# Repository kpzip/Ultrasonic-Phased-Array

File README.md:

# Ultrasonic-Phased-Array
play the vine boom with high precision

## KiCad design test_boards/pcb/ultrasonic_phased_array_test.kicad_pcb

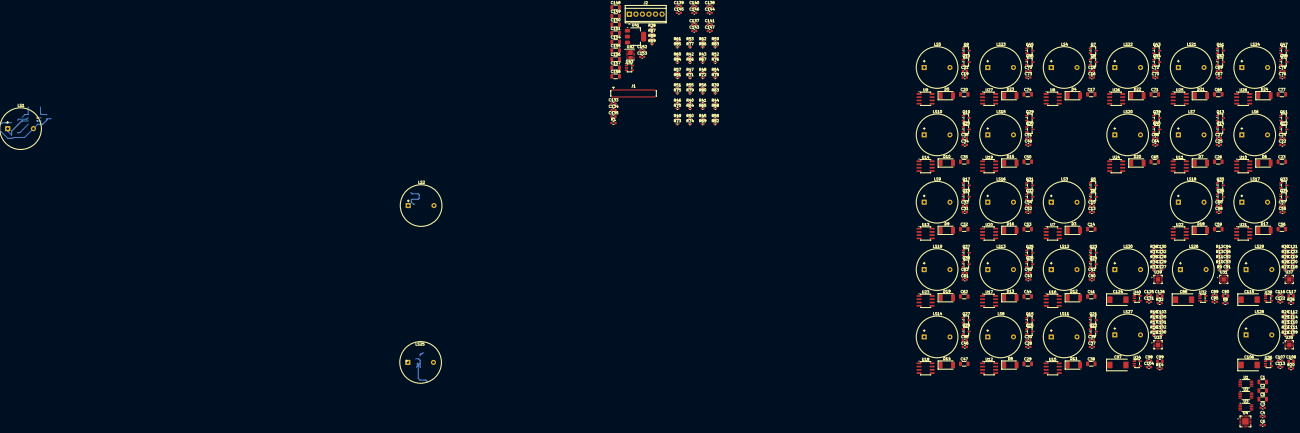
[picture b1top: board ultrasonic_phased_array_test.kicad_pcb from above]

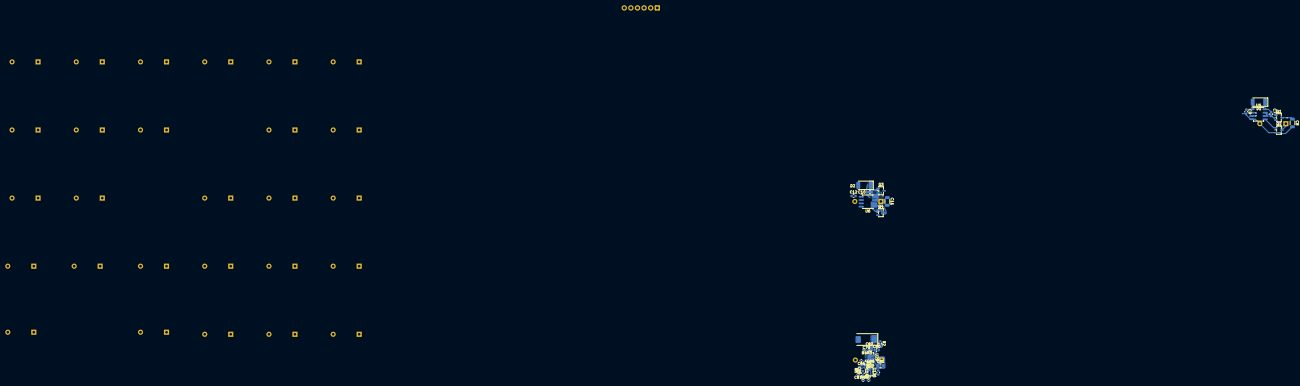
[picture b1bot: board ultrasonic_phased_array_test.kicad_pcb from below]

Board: 4 copper layers, 394 parts (33 on the bottom side), 298 nets.

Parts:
C1, C5, C148, C150, C151, C154, C155: 10μF; C_1206_3216Metric
C2, C156, C157, C158: 1μF; C_1206_3216Metric
C3, C4, C6, C9, C12, C15, C18, C21, C24, C27, C30, C33, C36, C39, C42, C45, C48, C51, C54, C57, C60, C63, C66, C69, C72, C75, C78, C80, C89, C98, C107, C116, C125, C133, C134, C135, C136, C137, C138, C139, C140, C141, C142, C143, C144, C145, C146, C147: 100nF; C_0603_1608Metric
C7, C10, C13, C16, C19, C22, C25, C28, C31, C34, C37, C40, C43, C46, C49, C52, C55, C58, C61, C64, C67, C70, C73, C76: 470nF; C_0603_1608Metric
C8, C11, C14, C17, C20, C23, C26, C29, C32, C35, C38, C41, C44, C47, C50, C53, C56, C59, C62, C65, C68, C71, C74, C77: 100nF; C_1206_3216Metric
C79, C88, C97, C106, C115, C124: 100μF; CP_EIA-7343-31_Kemet-D
C81, C90, C99, C108, C117, C126: 22nF; C_0805_2012Metric
C82, C91, C100, C109, C118, C127: 220pF; C_0402_1005Metric
C83, C84, C85, C87, C92, C93, C94, C96, C101, C102, C103, C105, C110, C111, C112, C114, C119, C120, C121, C123, C128, C129, C130, C132: 1nF; C_0402_1005Metric
C86, C95, C104, C113, C122, C131: 150nF; C_0603_1608Metric
C149: 22μF; C_1206_3216Metric
C152, C153: 10nF; C_0603_1608Metric
D1, D2, D3, D4, D5, D6, D7, D8, D9, D10, D11, D12, D13, D14, D15, D16, D17, D18, D19, D20, D21, D22, D23, D24: SUF4007; D_MELF
J1: DF40C-80DP-0.4V; Hirose_DF40C-80DP-0.4V_2x40-1MP_P0.4mm
J2: Screw_Terminal_01x06; TerminalBlock_TE_282834-6_1x06_P2.54mm_Horizontal
LS1, LS2, LS3, LS4, LS5, LS6, LS7, LS8, LS9, LS10, LS11, LS12, LS13, LS14, LS15, LS16, LS17, LS18, LS19, LS20, LS21, LS22, LS23, LS24, LS25, LS26, LS27, LS28, LS29, LS30: Speaker_Ultrasound; Ultrasonic_Transducer_D16mm_H7mm_P10mm
Q1, Q2, Q3, Q4, Q5, Q6, Q7, Q8, Q9, Q10, Q11, Q12, Q13, Q14, Q15, Q16, Q17, Q18, Q19, Q20, Q21, Q22, Q23, Q24, Q25, Q26, Q27, Q28, Q29, Q30, Q31, Q32, Q33, Q34, Q35, Q36, Q37, Q38, Q39, Q40, Q41, Q42, Q43, Q44, Q45, Q46, Q47, Q48: G2003A; SOT-23-3
R1, R2, R8, R14, R20, R26, R32: 10Ω; R_0603_1608Metric
R3, R9, R15, R21, R27, R33: 30kΩ; R_0402_1005Metric
R4, R10, R16, R22, R28, R34: 56kΩ; R_0402_1005Metric
R5, R11, R17, R23, R29, R35: 31.6kΩ; R_0402_1005Metric
R6, R12, R18, R24, R30, R36: 15.8kΩ; R_0402_1005Metric
R7, R13, R19, R25, R31, R37: 511Ω; R_0402_1005Metric
R38, R89: 24.3Ω; R_0402_1005Metric
R39, R40, R41, R42, R43, R44, R45, R46, R47, R48, R49, R50, R51, R52, R53, R54, R55, R56, R57, R58, R59, R60, R61, R62, R63, R64, R65, R66, R67, R68, R69, R70, R71, R72, R73, R74, R75, R76, R77, R78, R79, R80, R81, R82, R83, R84, R85, R86: 10kΩ; R_0402_1005Metric
R87, R88: 25.5Ω; R_0402_1005Metric
U1, U2, U3: OPA2626; Texas_S-PDSO-G8_3x3mm_P0.65mm
U4: AD7689xCP; LFCSP-20-1EP_4x4mm_P0.5mm_EP2.5x2.5mm
U5, U6, U7, U8, U9, U10, U11, U12, U13, U14, U15, U16, U17, U18, U19, U20, U21, U22, U23, U24, U25, U26, U27, U28: EG2131D; SOP-8_3.76x4.96mm_P1.27mm
U29, U31, U33, U35, U37, U39: LOG300RGT; VQFN-16-1EP_3x3mm_P0.5mm_EP1.68x1.68mm
U30, U32, U34, U36, U38, U40: OPA388xxDBV; SOT-23-5
U41: AZ1117CH-3.3; SOT-223-3_TabPin2
U42: LT3032; Linear_DE14MA
U43: TPS60401DBV; SOT-23-5

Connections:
+2.5V: C136.2, C137.2, C138.2, C139.2, C140.2, C141.2, C152.2, C154.2, R87.1, U30.5 (V+), U32.5 (V+), U34.5 (V+), U36.5 (V+), U38.5 (V+), U40.5 (V+), U42.1 (OUTP)
+3.3V: C3.2, C4.2, C149.1, U4.15 (VIO), U41.2 (OUT)
+5V: C1.2, C133.2, C134.2, C135.2, C148.2, C150.2, C158.2, J2.2, R1.2, R2.1, R8.1, R14.1, R20.1, R26.1, R32.1, U1.8 (V+), U2.8 (V+), U3.8 (V+), U41.3 (IN), U42.10 (~SHDNN), U42.12 (~SHDNP), U42.14 (INP), U43.2 (IN)
-2.5V: C142.1, C143.1, C144.1, C145.1, C146.1, C147.1, C153.2, C155.1, R88.2, U30.2 (V-), U32.2 (V-), U34.2 (V-), U36.2 (V-), U38.2 (V-), U40.2 (V-), U42.7 (OUTN)
-5V: C151.1, C157.2, U42.6 (INN), U42.9 (INN), U43.1 (OUT)
/ADC_CNV: J1.76, U4.11 (CNV)
/ADC_DIN: J1.77, U4.12 (DIN)
/ADC_SCK: J1.78, U4.13 (SCK)
/ADC_SDO: J1.75, U4.14 (SDO)
/Power & Regulators/ADJN: R88.1, R89.2, U42.8 (ADJN)
/Power & Regulators/ADJP: R38.1, R87.2, U42.2 (ADJP)
/TX1_HIN: J1.4, R39.2
/TX1_~LIN: J1.6, R63.1
/TX2_HIN: J1.10, R40.2
/TX2_~LIN: J1.12, R64.1
/TX3_HIN: J1.16, R41.2
/TX3_~LIN: J1.18, R65.1
/TX4_HIN: J1.22, R42.2
/TX4_~LIN: J1.24, R66.1
/TX5_HIN: J1.28, R43.2
/TX5_~LIN: J1.30, R67.1
/TX6_HIN: J1.34, R44.2
/TX6_~LIN: J1.36, R68.1
/TX7_HIN: J1.40, R45.2
/TX7_~LIN: J1.42, R69.1
/TX8_HIN: J1.46, R46.2
/TX8_~LIN: J1.48, R70.1
/TX9_HIN: J1.52, R47.2
/TX9_~LIN: J1.54, R71.1
/TX10_HIN: J1.58, R48.2
/TX10_~LIN: J1.60, R72.1
/TX11_HIN: J1.64, R49.2
/TX11_~LIN: J1.66, R73.1
/TX12_HIN: J1.70, R50.2
/TX12_~LIN: J1.72, R74.1
/TX13_HIN: J1.69, R51.2
/TX13_~LIN: J1.71, R75.1
/TX14_HIN: J1.63, R52.2
/TX14_~LIN: J1.65, R76.1
/TX15_HIN: J1.57, R53.2
/TX15_~LIN: J1.59, R77.1
/TX16_HIN: J1.51, R54.2
/TX16_~LIN: J1.53, R78.1
/TX17_HIN: J1.45, R55.2
/TX17_~LIN: J1.47, R79.1
/TX18_HIN: J1.39, R56.2
/TX18_~LIN: J1.41, R80.1
/TX19_HIN: J1.33, R57.2
/TX19_~LIN: J1.35, R81.1
/TX20_HIN: J1.27, R58.2
/TX20_~LIN: J1.29, R82.1
/TX21_HIN: J1.21, R59.2
/TX21_~LIN: J1.23, R83.1
/TX22_HIN: J1.15, R60.2
/TX22_~LIN: J1.17, R84.1
/TX23_HIN: J1.9, R61.2
/TX23_~LIN: J1.11, R85.1
/TX24_HIN: J1.3, R62.2
/TX24_~LIN: J1.5, R86.1
/Transducer Rx 1/OUTN: U1.3 (+), U29.6 (~BUFF)
/Transducer Rx 2/OUTN: U1.5 (+), U31.6 (~BUFF)
/Transducer Rx 3/OUTN: U2.3 (+), U33.6 (~BUFF)
/Transducer Rx 4/OUTN: U2.5 (+), U35.6 (~BUFF)
/Transducer Rx 5/OUTN: U3.3 (+), U37.6 (~BUFF)
/Transducer Rx 6/OUTN: U3.5 (+), U39.6 (~BUFF)
/Transducer Tx 1/HIN_IN: R39.1, U5.2 (HIN)
/Transducer Tx 1/~LIN_IN: R63.2, U5.3 (~LIN)
/Transducer Tx 2/HIN_IN: R40.1, U6.2 (HIN)
/Transducer Tx 2/~LIN_IN: R64.2, U6.3 (~LIN)
/Transducer Tx 3/HIN_IN: R41.1, U7.2 (HIN)
/Transducer Tx 3/~LIN_IN: R65.2, U7.3 (~LIN)
/Transducer Tx 4/HIN_IN: R42.1, U8.2 (HIN)
/Transducer Tx 4/~LIN_IN: R66.2, U8.3 (~LIN)
/Transducer Tx 5/HIN_IN: R43.1, U9.2 (HIN)
/Transducer Tx 5/~LIN_IN: R67.2, U9.3 (~LIN)
/Transducer Tx 6/HIN_IN: R44.1, U10.2 (HIN)
/Transducer Tx 6/~LIN_IN: R68.2, U10.3 (~LIN)
/Transducer Tx 7/HIN_IN: R45.1, U11.2 (HIN)
/Transducer Tx 7/~LIN_IN: R69.2, U11.3 (~LIN)
/Transducer Tx 8/HIN_IN: R46.1, U12.2 (HIN)
/Transducer Tx 8/~LIN_IN: R70.2, U12.3 (~LIN)
/Transducer Tx 9/HIN_IN: R47.1, U13.2 (HIN)
/Transducer Tx 9/~LIN_IN: R71.2, U13.3 (~LIN)
/Transducer Tx 10/HIN_IN: R48.1, U14.2 (HIN)
/Transducer Tx 10/~LIN_IN: R72.2, U14.3 (~LIN)
/Transducer Tx 11/HIN_IN: R49.1, U15.2 (HIN)
/Transducer Tx 11/~LIN_IN: R73.2, U15.3 (~LIN)
/Transducer Tx 12/HIN_IN: R50.1, U16.2 (HIN)
/Transducer Tx 12/~LIN_IN: R74.2, U16.3 (~LIN)
/Transducer Tx 13/HIN_IN: R51.1, U17.2 (HIN)
/Transducer Tx 13/~LIN_IN: R75.2, U17.3 (~LIN)
/Transducer Tx 14/HIN_IN: R52.1, U18.2 (HIN)
/Transducer Tx 14/~LIN_IN: R76.2, U18.3 (~LIN)
/Transducer Tx 15/HIN_IN: R53.1, U19.2 (HIN)
/Transducer Tx 15/~LIN_IN: R77.2, U19.3 (~LIN)
/Transducer Tx 16/HIN_IN: R54.1, U20.2 (HIN)
/Transducer Tx 16/~LIN_IN: R78.2, U20.3 (~LIN)
/Transducer Tx 17/HIN_IN: R55.1, U21.2 (HIN)
/Transducer Tx 17/~LIN_IN: R79.2, U21.3 (~LIN)
/Transducer Tx 18/HIN_IN: R56.1, U22.2 (HIN)
/Transducer Tx 18/~LIN_IN: R80.2, U22.3 (~LIN)
/Transducer Tx 19/HIN_IN: R57.1, U23.2 (HIN)
/Transducer Tx 19/~LIN_IN: R81.2, U23.3 (~LIN)
/Transducer Tx 20/HIN_IN: R58.1, U24.2 (HIN)
/Transducer Tx 20/~LIN_IN: R82.2, U24.3 (~LIN)
/Transducer Tx 21/HIN_IN: R59.1, U25.2 (HIN)
/Transducer Tx 21/~LIN_IN: R83.2, U25.3 (~LIN)
/Transducer Tx 22/HIN_IN: R60.1, U26.2 (HIN)
/Transducer Tx 22/~LIN_IN: R84.2, U26.3 (~LIN)
/Transducer Tx 23/HIN_IN: R61.1, U27.2 (HIN)
/Transducer Tx 23/~LIN_IN: R85.2, U27.3 (~LIN)
/Transducer Tx 24/HIN_IN: R62.1, U28.2 (HIN)
/Transducer Tx 24/~LIN_IN: R86.2, U28.3 (~LIN)
GND: C1.1, C2.1, C3.1, C4.1, C5.1, C6.1, C8.2, C9.2, C11.2, C12.2, C14.2, C15.2, C17.2, C18.2, C20.2, C21.2, C23.2, C24.2, C26.2, C27.2, C29.2, C30.2, C32.2, C33.2, C35.2, C36.2, C38.2, C39.2, C41.2, C42.2, C44.2, C45.2, C47.2, C48.2, C50.2, C51.2, C53.2, C54.2, C56.2, C57.2, C59.2, C60.2, C62.2, C63.2, C65.2, C66.2, C68.2, C69.2, C71.2, C72.2, C74.2, C75.2, C77.2, C78.2, C79.2, C80.1, C82.1, C84.2, C86.1, C88.2, C89.1, C91.1, C93.2, C95.1, C97.2, C98.1, C100.1, C102.2, C104.1, C106.2, C107.1, C109.1, C111.2, C113.1, C115.2, C116.1, C118.1, C120.2, C122.1, C124.2, C125.1, C127.1, C129.2, C131.1, C133.1, C134.1, C135.1, C136.1, C137.1, C138.1, C139.1, C140.1, C141.1, C142.2, C143.2, C144.2, C145.2, C146.2, C147.2, C148.1, C149.2, C157.1, C158.1, J1.1, J1.2, J1.7, J1.8, J1.13, J1.14, J1.19, J1.20, J1.25, J1.26, J1.31, J1.32, J1.37, J1.38, J1.43, J1.44, J1.49, J1.50, J1.55, J1.56, J1.61, J1.62, J1.67, J1.68, J1.73, J1.74, J1.79, J1.80, J2.1, J2.3, J2.5, LS1.2, LS2.2, LS3.2, LS4.2, LS5.2, LS6.2, LS7.2, LS8.2, LS9.2, LS10.2, LS11.2, LS12.2, LS13.2, LS14.2, LS15.2, LS16.2, LS17.2, LS18.2, LS19.2, LS20.2, LS21.2, LS22.2, LS23.2, LS24.2, LS25.2, LS26.2, LS27.2, LS28.2, LS29.2, LS30.2, Q2.2 (S), Q4.2 (S), Q6.2 (S), Q8.2 (S), Q10.2 (S), Q12.2 (S), Q14.2 (S), Q16.2 (S), Q18.2 (S), Q20.2 (S), Q22.2 (S), Q24.2 (S), Q26.2 (S), Q28.2 (S), Q30.2 (S), Q32.2 (S), Q34.2 (S), Q36.2 (S), Q38.2 (S), Q40.2 (S), Q42.2 (S), Q44.2 (S), Q46.2 (S), Q48.2 (S), R3.2, R4.2, R7.2, R9.2, R10.2, R13.2, R15.2, R16.2, R19.2, R21.2, R22.2, R25.2, R27.2, R28.2, R31.2, R33.2, R34.2, R37.2, U1.4 (V-), U2.4 (V-), U3.4 (V-), U4.4 (GND), U4.5 (GND), U4.10 (COM), U4.21 (EPAD), U5.4 (GND), U6.4 (GND), U7.4 (GND), U8.4 (GND), U9.4 (GND), U10.4 (GND), U11.4 (GND), U12.4 (GND), U13.4 (GND), U14.4 (GND), U15.4 (GND), U16.4 (GND), U17.4 (GND), U18.4 (GND), U19.4 (GND), U20.4 (GND), U21.4 (GND), U22.4 (GND), U23.4 (GND), U24.4 (GND), U25.4 (GND), U26.4 (GND), U27.4 (GND), U28.4 (GND), U29.10 (AGND), U29.15 (DGND), U29.17 (EP), U30.3 (+), U31.10 (AGND), U31.15 (DGND), U31.17 (EP), U32.3 (+), U33.10 (AGND), U33.15 (DGND), U33.17 (EP), U34.3 (+), U35.10 (AGND), U35.15 (DGND), U35.17 (EP), U36.3 (+), U37.10 (AGND), U37.15 (DGND), U37.17 (EP), U38.3 (+), U39.10 (AGND), U39.15 (DGND), U39.17 (EP), U40.3 (+), U41.1 (GND), U43.4 (GND)
unnamed: C2.2, R1.1, U4.1 (VDD), U4.20 (VDD)
unnamed: C81.1, LS25.1
unnamed: C83.2, C85.1, R5.2, U30.1
unnamed: C85.2, C87.2, R6.2, R7.1
unnamed: C90.1, LS26.1
unnamed: C92.2, C94.1, R11.2, U32.1
unnamed: C94.2, C96.2, R12.2, R13.1
unnamed: C99.1, LS27.1
unnamed: C101.2, C103.1, R17.2, U34.1
unnamed: C103.2, C105.2, R18.2, R19.1
unnamed: C108.1, LS28.1
unnamed: C110.2, C112.1, R23.2, U36.1
unnamed: C112.2, C114.2, R24.2, R25.1
unnamed: C117.1, LS29.1
unnamed: C119.2, C121.1, R29.2, U38.1
unnamed: C121.2, C123.2, R30.2, R31.1
unnamed: C126.1, LS30.1
unnamed: C128.2, C130.1, R35.2, U40.1
unnamed: C130.2, C132.2, R36.2, R37.1
unnamed: C7.1, D1.1 (K), U5.8 (VB)
unnamed: C10.1, D2.1 (K), U6.8 (VB)
unnamed: C13.1, D3.1 (K), U7.8 (VB)
unnamed: C16.1, D4.1 (K), U8.8 (VB)
unnamed: C19.1, D5.1 (K), U9.8 (VB)
unnamed: C22.1, D6.1 (K), U10.8 (VB)
unnamed: C25.1, D7.1 (K), U11.8 (VB)
unnamed: C28.1, D8.1 (K), U12.8 (VB)
unnamed: C31.1, D9.1 (K), U13.8 (VB)
unnamed: C34.1, D10.1 (K), U14.8 (VB)
unnamed: C37.1, D11.1 (K), U15.8 (VB)
unnamed: C40.1, D12.1 (K), U16.8 (VB)
unnamed: C43.1, D13.1 (K), U17.8 (VB)
unnamed: C46.1, D14.1 (K), U18.8 (VB)
unnamed: C49.1, D15.1 (K), U19.8 (VB)
unnamed: C52.1, D16.1 (K), U20.8 (VB)
unnamed: C55.1, D17.1 (K), U21.8 (VB)
unnamed: C58.1, D18.1 (K), U22.8 (VB)
unnamed: C61.1, D19.1 (K), U23.8 (VB)
unnamed: C64.1, D20.1 (K), U24.8 (VB)
unnamed: C67.1, D21.1 (K), U25.8 (VB)
unnamed: C70.1, D22.1 (K), U26.8 (VB)
unnamed: C73.1, D23.1 (K), U27.8 (VB)
unnamed: C76.1, D24.1 (K), U28.8 (VB)
unnamed: Q1.1 (G), U5.7 (HI)
unnamed: C7.2, LS1.1, Q1.2 (S), Q2.3 (D), U5.6 (SW)
unnamed: Q2.1 (G), U5.5 (LO)
unnamed: Q3.1 (G), U6.7 (HI)
unnamed: C10.2, LS2.1, Q3.2 (S), Q4.3 (D), U6.6 (SW)
unnamed: Q4.1 (G), U6.5 (LO)
unnamed: Q5.1 (G), U7.7 (HI)
unnamed: C13.2, LS3.1, Q5.2 (S), Q6.3 (D), U7.6 (SW)
unnamed: Q6.1 (G), U7.5 (LO)
unnamed: Q7.1 (G), U8.7 (HI)
unnamed: C16.2, LS4.1, Q7.2 (S), Q8.3 (D), U8.6 (SW)
unnamed: Q8.1 (G), U8.5 (LO)
unnamed: Q9.1 (G), U9.7 (HI)
unnamed: C19.2, LS5.1, Q9.2 (S), Q10.3 (D), U9.6 (SW)
unnamed: Q10.1 (G), U9.5 (LO)
unnamed: Q11.1 (G), U10.7 (HI)
unnamed: C22.2, LS6.1, Q11.2 (S), Q12.3 (D), U10.6 (SW)
unnamed: Q12.1 (G), U10.5 (LO)
unnamed: Q13.1 (G), U11.7 (HI)
unnamed: C25.2, LS7.1, Q13.2 (S), Q14.3 (D), U11.6 (SW)
unnamed: Q14.1 (G), U11.5 (LO)
unnamed: Q15.1 (G), U12.7 (HI)
unnamed: C28.2, LS8.1, Q15.2 (S), Q16.3 (D), U12.6 (SW)
unnamed: Q16.1 (G), U12.5 (LO)
unnamed: Q17.1 (G), U13.7 (HI)
unnamed: C31.2, LS9.1, Q17.2 (S), Q18.3 (D), U13.6 (SW)
unnamed: Q18.1 (G), U13.5 (LO)
unnamed: Q19.1 (G), U14.7 (HI)
unnamed: C34.2, LS10.1, Q19.2 (S), Q20.3 (D), U14.6 (SW)
unnamed: Q20.1 (G), U14.5 (LO)
unnamed: Q21.1 (G), U15.7 (HI)
unnamed: C37.2, LS11.1, Q21.2 (S), Q22.3 (D), U15.6 (SW)
unnamed: Q22.1 (G), U15.5 (LO)
unnamed: Q23.1 (G), U16.7 (HI)
unnamed: C40.2, LS12.1, Q23.2 (S), Q24.3 (D), U16.6 (SW)
unnamed: Q24.1 (G), U16.5 (LO)
unnamed: Q25.1 (G), U17.7 (HI)
unnamed: C43.2, LS13.1, Q25.2 (S), Q26.3 (D), U17.6 (SW)
unnamed: Q26.1 (G), U17.5 (LO)
unnamed: Q27.1 (G), U18.7 (HI)
unnamed: C46.2, LS14.1, Q27.2 (S), Q28.3 (D), U18.6 (SW)
unnamed: Q28.1 (G), U18.5 (LO)
unnamed: Q29.1 (G), U19.7 (HI)
unnamed: C49.2, LS15.1, Q29.2 (S), Q30.3 (D), U19.6 (SW)
unnamed: Q30.1 (G), U19.5 (LO)
unnamed: Q31.1 (G), U20.7 (HI)
unnamed: C52.2, LS16.1, Q31.2 (S), Q32.3 (D), U20.6 (SW)
unnamed: Q32.1 (G), U20.5 (LO)
unnamed: Q33.1 (G), U21.7 (HI)
unnamed: C55.2, LS17.1, Q33.2 (S), Q34.3 (D), U21.6 (SW)
unnamed: Q34.1 (G), U21.5 (LO)
unnamed: Q35.1 (G), U22.7 (HI)
unnamed: C58.2, LS18.1, Q35.2 (S), Q36.3 (D), U22.6 (SW)
unnamed: Q36.1 (G), U22.5 (LO)
unnamed: Q37.1 (G), U23.7 (HI)
unnamed: C61.2, LS19.1, Q37.2 (S), Q38.3 (D), U23.6 (SW)
unnamed: Q38.1 (G), U23.5 (LO)
unnamed: Q39.1 (G), U24.7 (HI)
unnamed: C64.2, LS20.1, Q39.2 (S), Q40.3 (D), U24.6 (SW)
unnamed: Q40.1 (G), U24.5 (LO)
unnamed: Q41.1 (G), U25.7 (HI)
unnamed: C67.2, LS21.1, Q41.2 (S), Q42.3 (D), U25.6 (SW)
unnamed: Q42.1 (G), U25.5 (LO)
unnamed: Q43.1 (G), U26.7 (HI)
unnamed: C70.2, LS22.1, Q43.2 (S), Q44.3 (D), U26.6 (SW)
unnamed: Q44.1 (G), U26.5 (LO)
unnamed: Q45.1 (G), U27.7 (HI)
unnamed: C73.2, LS23.1, Q45.2 (S), Q46.3 (D), U27.6 (SW)
unnamed: Q46.1 (G), U27.5 (LO)
unnamed: Q47.1 (G), U28.7 (HI)
unnamed: C76.2, LS24.1, Q47.2 (S), Q48.3 (D), U28.6 (SW)
unnamed: Q48.1 (G), U28.5 (LO)
unnamed: U1.1, U1.2 (-), U4.16 (IN0)
unnamed: U1.6 (-), U1.7, U4.17 (IN1)
unnamed: U2.1, U2.2 (-), U4.18 (IN2)
unnamed: U2.6 (-), U2.7, U4.19 (IN3)
unnamed: U3.1, U3.2 (-), U4.6 (IN4)
unnamed: U3.6 (-), U3.7, U4.7 (IN5)
unnamed: C5.2, U4.2 (REF)
unnamed: C6.2, U4.3 (REFIN)
unnamed: C79.1, C80.2, R2.2, U29.1 (VCC), U29.14 (AFE_EN), U29.16 (LNA_EN)
unnamed: C81.2, U29.13 (LNA_IN)
unnamed: R6.1, U29.11 (LNA_OUT)
unnamed: C84.1, U29.8 (LOG_INN)
unnamed: C83.1, U29.9 (LOG_INP)
unnamed: C82.2, R3.1, U29.2 (LOG_OUT)
unnamed: C86.2, U29.12 (OFFSET_CAP)
unnamed: R4.1, U29.3 (REF_RES)
unnamed: C87.1, R5.1, U30.4 (-)
unnamed: C88.1, C89.2, R8.2, U31.1 (VCC), U31.14 (AFE_EN), U31.16 (LNA_EN)
unnamed: C90.2, U31.13 (LNA_IN)
unnamed: R12.1, U31.11 (LNA_OUT)
unnamed: C93.1, U31.8 (LOG_INN)
unnamed: C92.1, U31.9 (LOG_INP)
unnamed: C91.2, R9.1, U31.2 (LOG_OUT)
unnamed: C95.2, U31.12 (OFFSET_CAP)
unnamed: R10.1, U31.3 (REF_RES)
unnamed: C96.1, R11.1, U32.4 (-)
unnamed: C97.1, C98.2, R14.2, U33.1 (VCC), U33.14 (AFE_EN), U33.16 (LNA_EN)
unnamed: C99.2, U33.13 (LNA_IN)
unnamed: R18.1, U33.11 (LNA_OUT)
unnamed: C102.1, U33.8 (LOG_INN)
unnamed: C101.1, U33.9 (LOG_INP)
unnamed: C100.2, R15.1, U33.2 (LOG_OUT)
unnamed: C104.2, U33.12 (OFFSET_CAP)
unnamed: R16.1, U33.3 (REF_RES)
unnamed: C105.1, R17.1, U34.4 (-)
unnamed: C106.1, C107.2, R20.2, U35.1 (VCC), U35.14 (AFE_EN), U35.16 (LNA_EN)
unnamed: C108.2, U35.13 (LNA_IN)
unnamed: R24.1, U35.11 (LNA_OUT)
unnamed: C111.1, U35.8 (LOG_INN)
unnamed: C110.1, U35.9 (LOG_INP)
unnamed: C109.2, R21.1, U35.2 (LOG_OUT)
unnamed: C113.2, U35.12 (OFFSET_CAP)
unnamed: R22.1, U35.3 (REF_RES)
unnamed: C114.1, R23.1, U36.4 (-)
unnamed: C115.1, C116.2, R26.2, U37.1 (VCC), U37.14 (AFE_EN), U37.16 (LNA_EN)
unnamed: C117.2, U37.13 (LNA_IN)
unnamed: R30.1, U37.11 (LNA_OUT)
unnamed: C120.1, U37.8 (LOG_INN)
unnamed: C119.1, U37.9 (LOG_INP)
unnamed: C118.2, R27.1, U37.2 (LOG_OUT)
unnamed: C122.2, U37.12 (OFFSET_CAP)
unnamed: R28.1, U37.3 (REF_RES)
unnamed: C123.1, R29.1, U38.4 (-)
unnamed: C124.1, C125.2, R32.2, U39.1 (VCC), U39.14 (AFE_EN), U39.16 (LNA_EN)
unnamed: C126.2, U39.13 (LNA_IN)
unnamed: R36.1, U39.11 (LNA_OUT)
unnamed: C129.1, U39.8 (LOG_INN)
unnamed: C128.1, U39.9 (LOG_INP)
unnamed: C127.2, R33.1, U39.2 (LOG_OUT)
unnamed: C131.2, U39.12 (OFFSET_CAP)
unnamed: R34.1, U39.3 (REF_RES)
unnamed: C132.1, R35.1, U40.4 (-)
unnamed: C152.1, U42.3 (BYPP)
unnamed: C150.1, C151.2, C154.1, C155.2, R38.2, R89.1, U42.4 (GND), U42.5 (GND)
unnamed: C153.1, U42.11 (BYPN)
unnamed: C156.2, U43.5 (C_{FLY+})
unnamed: C156.1, U43.3 (C_{FLY-})
VGD: C9.1, C12.1, C15.1, C18.1, C21.1, C24.1, C27.1, C30.1, C33.1, C36.1, C39.1, C42.1, C45.1, C48.1, C51.1, C54.1, C57.1, C60.1, C63.1, C66.1, C69.1, C72.1, C75.1, C78.1, D1.2 (A), D2.2 (A), D3.2 (A), D4.2 (A), D5.2 (A), D6.2 (A), D7.2 (A), D8.2 (A), D9.2 (A), D10.2 (A), D11.2 (A), D12.2 (A), D13.2 (A), D14.2 (A), D15.2 (A), D16.2 (A), D17.2 (A), D18.2 (A), D19.2 (A), D20.2 (A), D21.2 (A), D22.2 (A), D23.2 (A), D24.2 (A), J2.4, U5.1 (VCC), U6.1 (VCC), U7.1 (VCC), U8.1 (VCC), U9.1 (VCC), U10.1 (VCC), U11.1 (VCC), U12.1 (VCC), U13.1 (VCC), U14.1 (VCC), U15.1 (VCC), U16.1 (VCC), U17.1 (VCC), U18.1 (VCC), U19.1 (VCC), U20.1 (VCC), U21.1 (VCC), U22.1 (VCC), U23.1 (VCC), U24.1 (VCC), U25.1 (VCC), U26.1 (VCC), U27.1 (VCC), U28.1 (VCC)
VSPK: C8.1, C11.1, C14.1, C17.1, C20.1, C23.1, C26.1, C29.1, C32.1, C35.1, C38.1, C41.1, C44.1, C47.1, C50.1, C53.1, C56.1, C59.1, C62.1, C65.1, C68.1, C71.1, C74.1, C77.1, J2.6, Q1.3 (D), Q3.3 (D), Q5.3 (D), Q7.3 (D), Q9.3 (D), Q11.3 (D), Q13.3 (D), Q15.3 (D), Q17.3 (D), Q19.3 (D), Q21.3 (D), Q23.3 (D), Q25.3 (D), Q27.3 (D), Q29.3 (D), Q31.3 (D), Q33.3 (D), Q35.3 (D), Q37.3 (D), Q39.3 (D), Q41.3 (D), Q43.3 (D), Q45.3 (D), Q47.3 (D)
